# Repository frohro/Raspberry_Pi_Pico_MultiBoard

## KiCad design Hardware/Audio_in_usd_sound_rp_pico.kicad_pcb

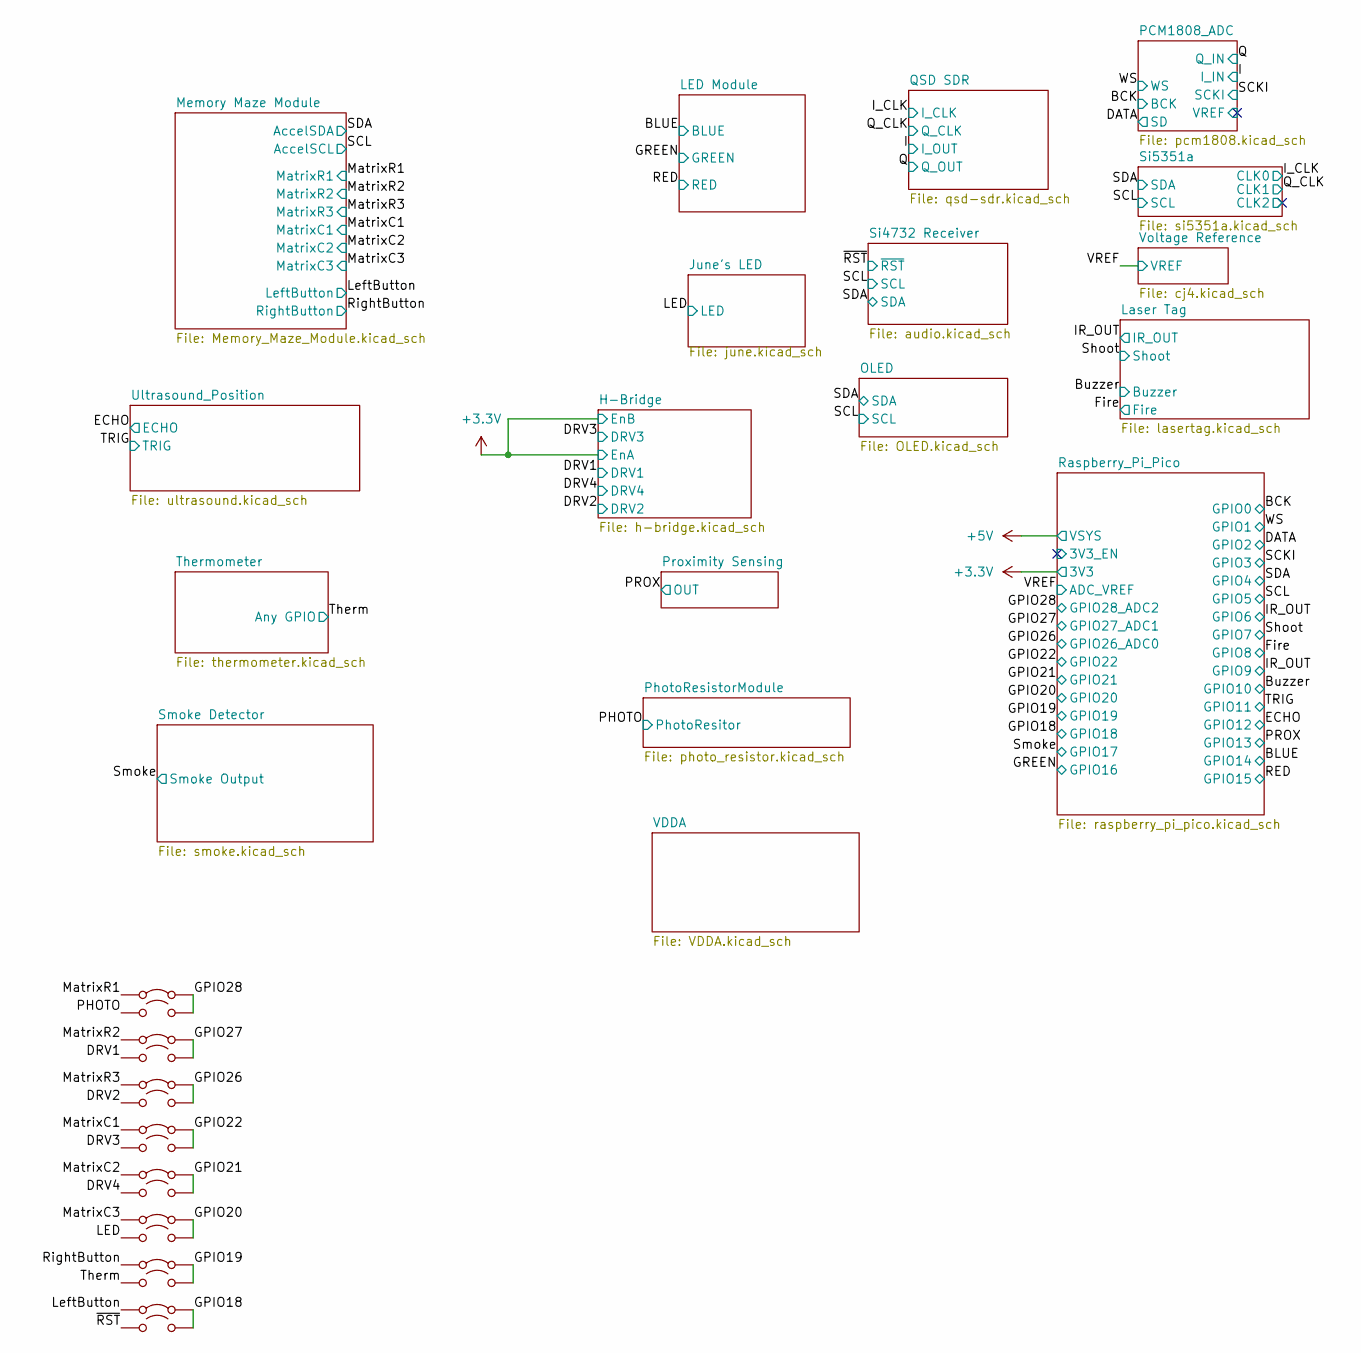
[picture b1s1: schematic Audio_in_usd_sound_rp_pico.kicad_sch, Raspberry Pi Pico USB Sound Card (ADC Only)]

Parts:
JP1, JP3, JP5, JP7, JP9, JP11, JP13, JP15: Jumper_2_Bridged; SolderJumper-2_P1.3mm_Bridged2Bar_RoundedPad1.0x1.5mm
JP2, JP4, JP6, JP8, JP10, JP12, JP14, JP16: Jumper_2_Open; SolderJumper-2_P1.3mm_Open_RoundedPad1.0x1.5mm

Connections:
/DRV1: JP4.1 (A); also elsewhere on the board
/DRV2: JP6.1 (A); also elsewhere on the board
/DRV3: JP8.1 (A); also elsewhere on the board
/DRV4: JP10.1 (A); also elsewhere on the board
/GPIO18: JP15.2 (B), JP16.2 (B); also elsewhere on the board
/GPIO19: JP13.2 (B), JP14.2 (B); also elsewhere on the board
/GPIO20: JP11.2 (B), JP12.2 (B); also elsewhere on the board
/GPIO21: JP9.2 (B), JP10.2 (B); also elsewhere on the board
/GPIO22: JP7.2 (B), JP8.2 (B); also elsewhere on the board
/GPIO26: JP5.2 (B), JP6.2 (B); also elsewhere on the board
/GPIO27: JP3.2 (B), JP4.2 (B); also elsewhere on the board
/GPIO28: JP1.2 (B), JP2.2 (B); also elsewhere on the board
/LED: JP12.1 (A); also elsewhere on the board
/LeftButton: JP15.1 (A); also elsewhere on the board
/MatrixC1: JP7.1 (A); also elsewhere on the board
/MatrixC2: JP9.1 (A); also elsewhere on the board
/MatrixC3: JP11.1 (A); also elsewhere on the board
/MatrixR1: JP1.1 (A); also elsewhere on the board
/MatrixR2: JP3.1 (A); also elsewhere on the board
/MatrixR3: JP5.1 (A); also elsewhere on the board
/PHOTO: JP2.1 (A); also elsewhere on the board
/RightButton: JP13.1 (A); also elsewhere on the board
/Therm: JP14.1 (A); also elsewhere on the board
/~RST: JP16.1 (A); also elsewhere on the board

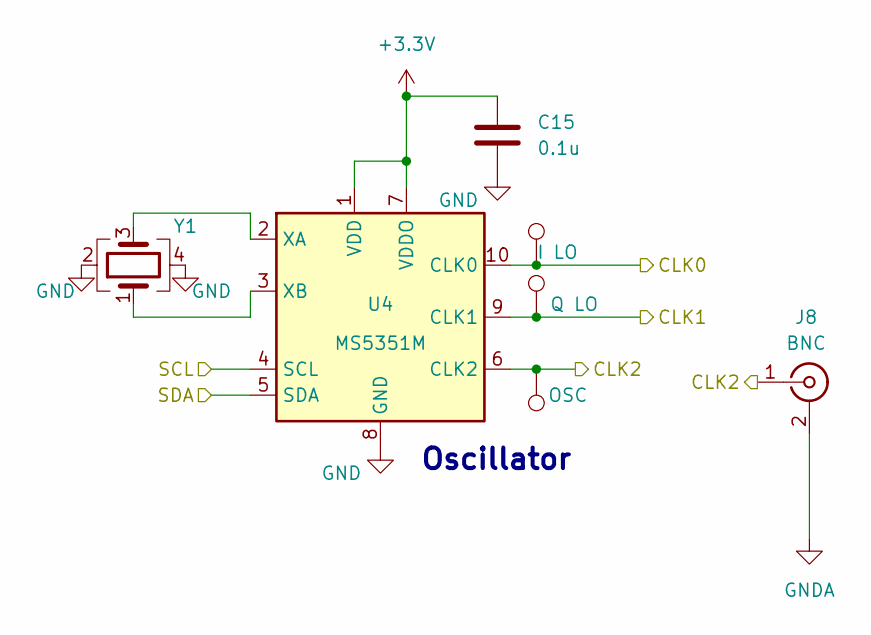
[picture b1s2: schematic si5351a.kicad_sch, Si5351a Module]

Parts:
C15: 0.1u; C_0805_2012Metric; LCSC C49678
J8: BNC; BNC_TEConnectivity_1478204_Vertical
TP3: I LO; TestPoint_THTPad_D1.0mm_Drill0.5mm
TP4: Q LO; TestPoint_THTPad_D1.0mm_Drill0.5mm
TP5: OSC; TestPoint_THTPad_D1.0mm_Drill0.5mm
U4: MS5351M; MSOP-10_3x3mm_P0.5mm; LCSC C1509083
Y1: X322525MSB4SI; Crystal_SMD_3225-4Pin_3.2x2.5mm; LCSC C9006

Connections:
+3.3V: C15.2, U4.1 (VDD), U4.7 (VDDO); also elsewhere on the board
/I_CLK: TP3.1, U4.10 (CLK0); also elsewhere on the board
/Q_CLK: TP4.1, U4.9 (CLK1); also elsewhere on the board
/SCL: U4.4 (SCL); also elsewhere on the board
/SDA: U4.5 (SDA); also elsewhere on the board
/Si5351a/CLK2: J8.1 (In), TP5.1, U4.6 (CLK2)
GND: C15.1, J8.2 (Ext), U4.8 (GND), Y1.2, Y1.4; also elsewhere on the board
unnamed: U4.2 (XA), Y1.3
unnamed: U4.3 (XB), Y1.1

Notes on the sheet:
Oscillator

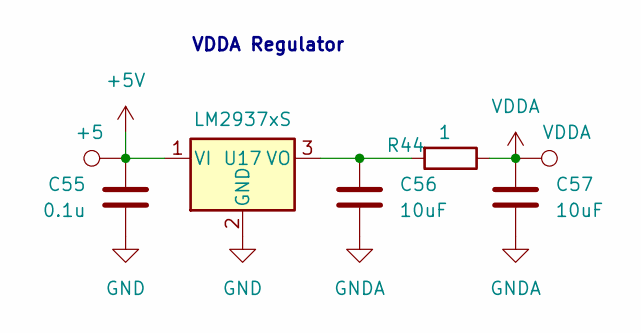
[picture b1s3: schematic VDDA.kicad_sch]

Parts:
C55: 0.1u; C_0805_2012Metric; LCSC C49678
C56, C57: 10uF; C_0805_2012Metric; LCSC C15850
R44: 1; R_0805_2012Metric; LCSC C25271
TP25: +5; TestPoint_THTPad_D1.0mm_Drill0.5mm
TP26: VDDA; TestPoint_THTPad_D1.0mm_Drill0.5mm
U17: LM2937xS; TO-263-3_TabPin2; LCSC C2902486

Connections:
+5V: C55.1, TP25.1, U17.1 (VI); also elsewhere on the board
GND: C55.2, C56.2, C57.2, U17.2 (GND); also elsewhere on the board
unnamed: C56.1, R44.2, U17.3 (VO)
VDDA: C57.1, R44.1, TP26.1; also elsewhere on the board

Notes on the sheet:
VDDA Regulator

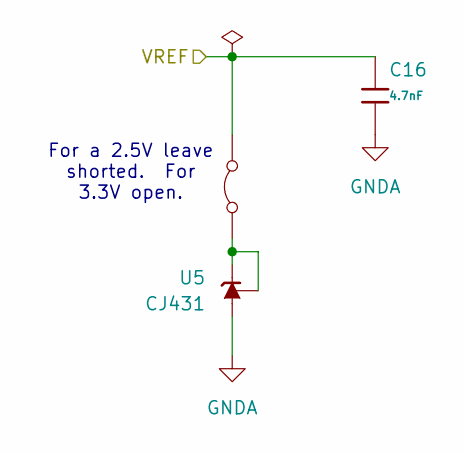
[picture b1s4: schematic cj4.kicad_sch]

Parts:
C16: 4.7nF; C_0805; Voltage Rated 50V; Tolerance ±10%; Part 0805B472K500NT; LCSC C1744
JP84: Jumper_2_Bridged; SolderJumper-2_P1.3mm_Bridged2Bar_RoundedPad1.0x1.5mm
U5: CJ431; SOT-23; JLCPCB Rotation Offset 180

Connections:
/VREF: C16.1, JP84.2 (B); also elsewhere on the board
GND: C16.2, U5.3 (A); also elsewhere on the board
unnamed: JP84.1 (A), U5.1 (REF), U5.2 (K)

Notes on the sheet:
For a 2.5V leave shorted. For 3.3V open.

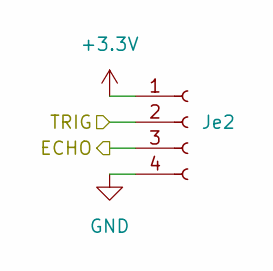
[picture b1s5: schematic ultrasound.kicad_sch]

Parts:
Je2: Conn_01x04_Socket; PinHeader_1x04_P2.54mm_Vertical_Female; LCSC C2718488

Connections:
+3.3V: Je2.1; also elsewhere on the board
/ECHO: Je2.3; also elsewhere on the board
/TRIG: Je2.2; also elsewhere on the board
GND: Je2.4; also elsewhere on the board

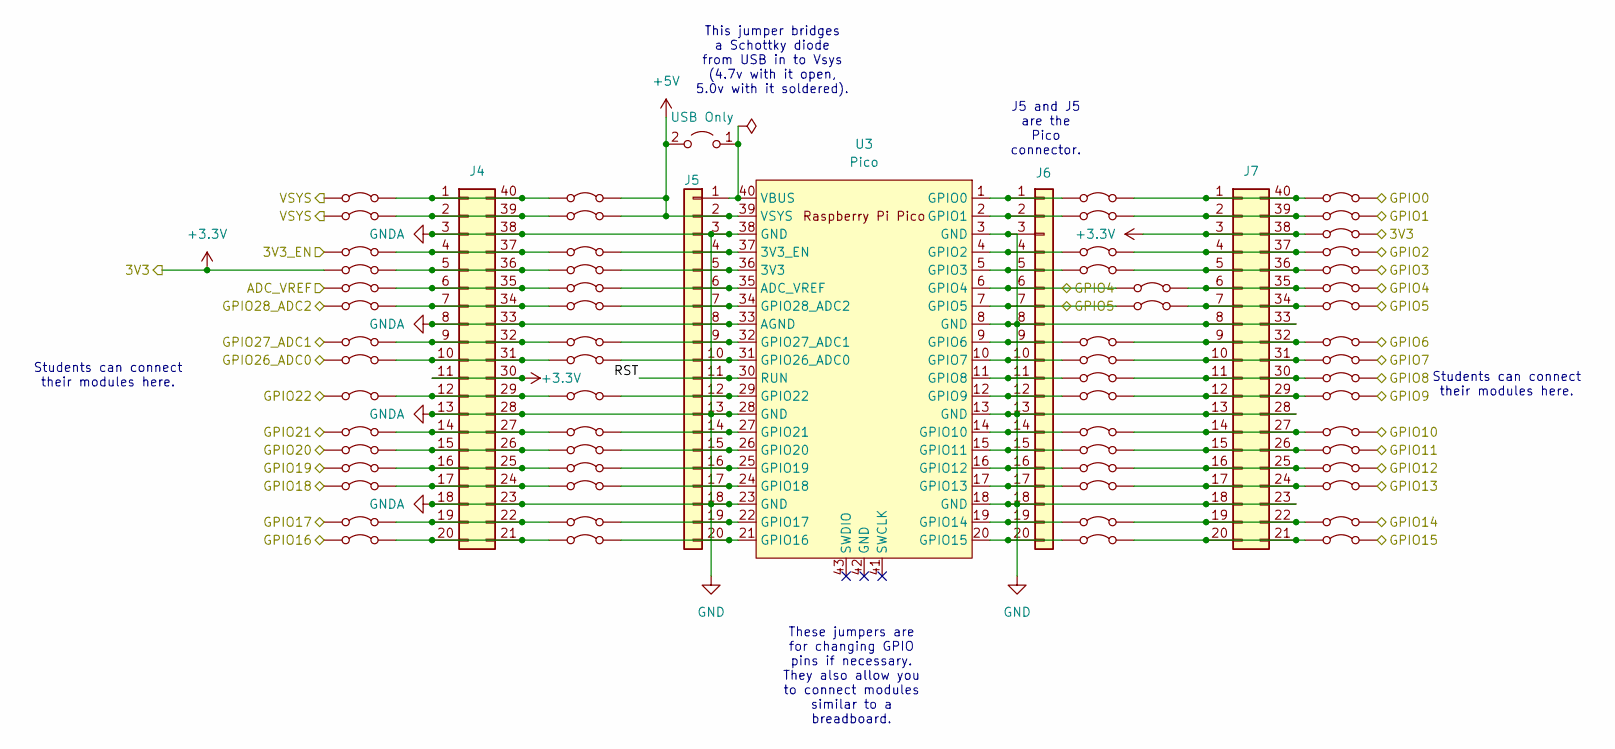
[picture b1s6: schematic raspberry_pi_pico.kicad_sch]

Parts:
J4: Conn_02x20_Counter_Clockwise; PinSocket_2x20_P2.54mm_Vertical_Counterclockwise; LCSC C2977589
J5, J6: Conn_01x20; PinHeader_1x20_P2.54mm_Vertical; LCSC C2905423
J7: Conn_02x20_Counter_Clockwise; PinSocket_2x20_P2.54mm_Vertical; LCSC C2977589
JP20, JP21, JP22, JP23, JP24, JP25, JP26, JP27, JP28, JP29, JP30, JP31, JP32, JP33, JP34, JP35, JP36, JP37, JP38, JP39, JP40, JP41, JP42, JP43, JP44, JP45, JP46, JP47, JP48, JP49, JP51, JP52, JP53, JP54, JP55, JP56, JP57, JP58, JP59, JP60, JP61, JP62, JP63, JP64, JP65, JP66, JP67, JP68, JP69, JP70, JP71, JP72, JP73, JP74, JP75, JP76, JP77, JP78, JP79, JP80, JP81, JP82, JP83: Jumper_2_Bridged; SolderJumper-2_P1.3mm_Bridged2Bar_RoundedPad1.0x1.5mm
JP50: USB Only; SolderJumper-2_P1.3mm_Open_RoundedPad1.0x1.5mm
U3: Pico; RPi_Pico_SMD_TH

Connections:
+3.3V: J4.11, J4.30, J7.3, J7.38, JP23.1 (A), JP69.1 (A), JP69.2 (B); also elsewhere on the board
+5V: J5.2, JP20.1 (A), JP21.1 (A), JP35.2 (B), JP36.2 (B), JP50.2 (B), U3.39 (VSYS); also elsewhere on the board
/BCK: JP67.2 (B); also elsewhere on the board
/BLUE: JP82.2 (B); also elsewhere on the board
/Buzzer: JP78.2 (B); also elsewhere on the board
/DATA: JP70.2 (B); also elsewhere on the board
/ECHO: JP80.2 (B); also elsewhere on the board
/Fire: JP76.2 (B); also elsewhere on the board
/GPIO18: JP32.1 (A); also elsewhere on the board
/GPIO19: JP31.1 (A); also elsewhere on the board
/GPIO20: JP30.1 (A); also elsewhere on the board
/GPIO21: JP29.1 (A); also elsewhere on the board
/GPIO22: JP28.1 (A); also elsewhere on the board
/GPIO26: JP27.1 (A); also elsewhere on the board
/GPIO27: JP26.1 (A); also elsewhere on the board
/GPIO28: JP25.1 (A); also elsewhere on the board
/GREEN: JP34.1 (A); also elsewhere on the board
/IR_OUT: JP74.2 (B), JP77.2 (B); also elsewhere on the board
/PROX: JP81.2 (B); also elsewhere on the board
/RED: JP83.2 (B); also elsewhere on the board
/Raspberry_Pi_Pico/3V3_EN: JP22.1 (A)
/Raspberry_Pi_Pico/RST: J5.11, U3.30 (RUN)
/SCKI: JP71.2 (B); also elsewhere on the board
/SCL: J6.7, JP56.1 (A), JP73.2 (B), U3.7 (GPIO5); also elsewhere on the board
/SDA: J6.6, JP55.1 (A), JP72.2 (B), U3.6 (GPIO4); also elsewhere on the board
/Shoot: JP75.2 (B); also elsewhere on the board
/Smoke: JP33.1 (A); also elsewhere on the board
/TRIG: JP79.2 (B); also elsewhere on the board
/VREF: JP24.1 (A); also elsewhere on the board
/WS: JP68.2 (B); also elsewhere on the board
GND: J4.3, J4.8, J4.13, J4.18, J4.23, J4.28, J4.33, J4.38, J5.3, J5.8, J5.13, J5.18, J6.3, J6.8, J6.13, J6.18, J7.8, J7.13, J7.18, J7.23, J7.28, J7.33, U3.3 (GND), U3.8 (GND), U3.13 (GND), U3.18 (GND), U3.23 (GND), U3.28 (GND), U3.33 (AGND), U3.38 (GND); also elsewhere on the board
unnamed: J4.1, J4.40, JP20.2 (B), JP35.1 (A)
unnamed: J4.2, J4.39, JP21.2 (B), JP36.1 (A)
unnamed: J4.10, J4.31, JP27.2 (B), JP42.1 (A)
unnamed: J4.12, J4.29, JP28.2 (B), JP43.1 (A)
unnamed: J4.14, J4.27, JP29.2 (B), JP44.1 (A)
unnamed: J4.15, J4.26, JP30.2 (B), JP45.1 (A)
unnamed: J4.16, J4.25, JP31.2 (B), JP46.1 (A)
unnamed: J4.17, J4.24, JP32.2 (B), JP47.1 (A)
unnamed: J4.19, J4.22, JP33.2 (B), JP48.1 (A)
unnamed: J4.20, J4.21, JP34.2 (B), JP49.1 (A)
unnamed: J4.9, J4.32, JP26.2 (B), JP41.1 (A)
unnamed: J4.7, J4.34, JP25.2 (B), JP40.1 (A)
unnamed: J4.6, J4.35, JP24.2 (B), JP39.1 (A)
unnamed: J4.5, J4.36, JP23.2 (B), JP38.1 (A)
unnamed: J4.4, J4.37, JP22.2 (B), JP37.1 (A)
unnamed: J5.1, JP50.1 (A), U3.40 (VBUS)
unnamed: J5.4, JP37.2 (B), U3.37 (3V3_EN)
unnamed: J5.5, JP38.2 (B), U3.36 (3V3)
unnamed: J5.6, JP39.2 (B), U3.35 (ADC_VREF)
unnamed: J5.7, JP40.2 (B), U3.34 (GPIO28_ADC2)
unnamed: J5.9, JP41.2 (B), U3.32 (GPIO27_ADC1)
unnamed: J5.10, JP42.2 (B), U3.31 (GPIO26_ADC0)
unnamed: J5.12, JP43.2 (B), U3.29 (GPIO22)
unnamed: J5.14, JP44.2 (B), U3.27 (GPIO21)
unnamed: J5.15, JP45.2 (B), U3.26 (GPIO20)
unnamed: J5.16, JP46.2 (B), U3.25 (GPIO19)
unnamed: J5.17, JP47.2 (B), U3.24 (GPIO18)
unnamed: J5.19, JP48.2 (B), U3.22 (GPIO17)
unnamed: J5.20, JP49.2 (B), U3.21 (GPIO16)
unnamed: J6.1, JP51.1 (A), U3.1 (GPIO0)
unnamed: J6.2, JP52.1 (A), U3.2 (GPIO1)
unnamed: J6.4, JP53.1 (A), U3.4 (GPIO2)
unnamed: J6.5, JP54.1 (A), U3.5 (GPIO3)
unnamed: J6.9, JP57.1 (A), U3.9 (GPIO6)
unnamed: J6.10, JP58.1 (A), U3.10 (GPIO7)
unnamed: J6.11, JP59.1 (A), U3.11 (GPIO8)
unnamed: J6.12, JP60.1 (A), U3.12 (GPIO9)
unnamed: J6.14, JP61.1 (A), U3.14 (GPIO10)
unnamed: J6.15, JP62.1 (A), U3.15 (GPIO11)
unnamed: J6.16, JP63.1 (A), U3.16 (GPIO12)
unnamed: J6.17, JP64.1 (A), U3.17 (GPIO13)
unnamed: J6.19, JP65.1 (A), U3.19 (GPIO14)
unnamed: J6.20, JP66.1 (A), U3.20 (GPIO15)
unnamed: J7.1, J7.40, JP51.2 (B), JP67.1 (A)
unnamed: J7.2, J7.39, JP52.2 (B), JP68.1 (A)
unnamed: J7.10, J7.31, JP58.2 (B), JP75.1 (A)
unnamed: J7.11, J7.30, JP59.2 (B), JP76.1 (A)
unnamed: J7.12, J7.29, JP60.2 (B), JP77.1 (A)
unnamed: J7.14, J7.27, JP61.2 (B), JP78.1 (A)
unnamed: J7.15, J7.26, JP62.2 (B), JP79.1 (A)
unnamed: J7.16, J7.25, JP63.2 (B), JP80.1 (A)
unnamed: J7.17, J7.24, JP64.2 (B), JP81.1 (A)
unnamed: J7.19, J7.22, JP65.2 (B), JP82.1 (A)
unnamed: J7.20, J7.21, JP66.2 (B), JP83.1 (A)
unnamed: J7.9, J7.32, JP57.2 (B), JP74.1 (A)
unnamed: J7.7, J7.34, JP56.2 (B), JP73.1 (A)
unnamed: J7.6, J7.35, JP55.2 (B), JP72.1 (A)
unnamed: J7.5, J7.36, JP54.2 (B), JP71.1 (A)
unnamed: J7.4, J7.37, JP53.2 (B), JP70.1 (A)

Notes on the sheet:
These jumpers are for changing GPIO pins if necessary. They also allow you to connect modules similar to a breadboard.
Students can connect their modules here.
J5 and J5 are the Pico connector.
This jumper bridges a Schottky diode from USB in to Vsys (4.7v with it open, 5.0v with it soldered).

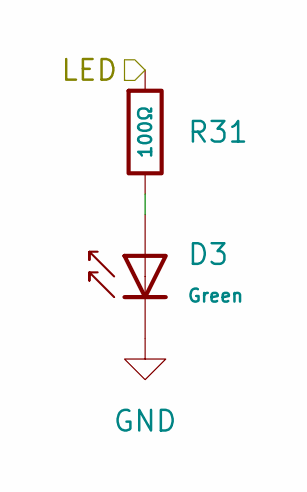
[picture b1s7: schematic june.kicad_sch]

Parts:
D3: Green; D_0805; Part KT-0805G; LCSC C2297
R31: 100Ω; R_0805; Overload Voltage (Max) 150V; Tolerance ±1%; Part 0805W8F1000T5E; LCSC C17408

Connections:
/LED: R31.1; also elsewhere on the board
GND: D3.1; also elsewhere on the board
unnamed: D3.2, R31.2

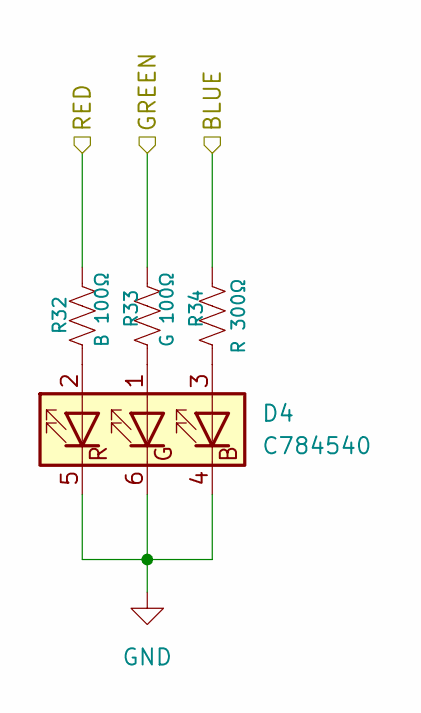
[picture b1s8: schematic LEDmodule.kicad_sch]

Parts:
D4: C784540; LED footprint; LCSC C784540
R32: B 100Ω; L_0805_2012Metric; JLCPCB# C25277
R33: G 100Ω; L_0805_2012Metric; JLCPCB# C25277
R34: R 300Ω; R_0805_2012Metric; JLCPCB# C168494

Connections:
/BLUE: R34.1; also elsewhere on the board
/GREEN: R33.1; also elsewhere on the board
/RED: R32.1; also elsewhere on the board
GND: D4.4 (BK), D4.5 (RK), D4.6 (GK); also elsewhere on the board
unnamed: D4.3 (BA), R34.2
unnamed: D4.1 (GA), R33.2
unnamed: D4.2 (RA), R32.2

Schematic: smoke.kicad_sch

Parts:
R43: 100Ω; R_0805; Overload Voltage (Max) 150V; Tolerance ±1%; Part 0805W8F1000T5E; LCSC C17408
U16: TO-33-4_Window-Taylan; LCSC C5380082

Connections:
+3.3V: U16.3 (VC); also elsewhere on the board
+5V: U16.1 (V0_1); also elsewhere on the board
/Smoke: R43.1, U16.4 (V(RL)); also elsewhere on the board
<NO NET>: R43.2, U16.2 (V0_2)

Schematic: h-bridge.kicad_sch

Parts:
C49, C50: 100nF; C_0805; Voltage Rated 50V; Tolerance ±10%; Part CC0805KRX7R9BB104; LCSC C49678
D5, D6, D7, D8, D9, D10, D11, D12: 1N4004W; D_SOD-123FL; Forward Voltage (Vf@If) 1V@1.0A; Reverse Voltage (Vr) 400V; Part 1N4004W; LCSC C18199087
J16: Audio IN; Jack_3.5mm_CUI_SJ-3523-SMT_Horizontal; LCSC C18594
JP89: Jumper_2_Bridged; SolderJumper-2_P1.3mm_Bridged2Bar_RoundedPad1.0x1.5mm
T1, T2: Screw Terminal, 4Px5.08mm, 20A; CONN-TH_4P-P5.08_DB129VG-5.08-4P-GN-S; Current Rating (Max) 20A; Voltage Rating (Max) 300V; Part DB129VG-5.08-4P-GN-S; LCSC C2981774
U12: L298N; TO-220-15_P2.54x2.54mm_StaggerOdd_Lead4.58mm_Vertical; JLCPCB part # C19922

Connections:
+3.3V: U12.6 (EnA), U12.11 (EnB); also elsewhere on the board
+5V: JP89.1 (A), U12.9 (Vss); also elsewhere on the board
/DRV1: U12.5 (IN1); also elsewhere on the board
/DRV2: U12.7 (IN2); also elsewhere on the board
/DRV3: U12.10 (IN3); also elsewhere on the board
/DRV4: U12.12 (IN4); also elsewhere on the board
GND: C49.2, C50.2, D6.2, D8.2, D10.2, D12.2, J16.S, T1.4, U12.8 (GND); also elsewhere on the board
unnamed: D7.2, D8.1, J16.R, T2.1, U12.2 (OUT1)
unnamed: D11.2, D12.1, J16.T, T2.2, U12.3 (OUT2)
unnamed: D5.2, D6.1, T2.3, U12.13 (OUT3)
unnamed: D9.2, D10.1, T2.4, U12.14 (OUT4)
unnamed: T1.2, U12.1 (SENSE_A)
unnamed: T1.1, U12.15 (SENSE_B)
VS: C49.1, C50.1, D5.1, D7.1, D9.1, D11.1, JP89.2 (B), T1.3, U12.4 (Vs)

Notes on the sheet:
Resistors

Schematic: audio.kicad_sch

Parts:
C33, C42: 220pF; C_0805; Voltage Rated 50V; Tolerance ±10%; Part CC0805KRX7R9BB221; LCSC C107145
C34, C43: 10nF; C_0603; Voltage Rated 50V; Tolerance ±10%; Part 0603B103K500NT; LCSC C57112
C35, C54: 2.2nF; C_0603; Voltage Rated 50V; Tolerance ±10%; Part 0603B222K500NT; LCSC C1604
C36, C37: 22pF; C_0603; Voltage Rated 50V; Tolerance ±5%; Part CL10C220JB8NNNC; LCSC C1653
C38, C41, C52: 100nF; C_0603; Voltage Rated 50V; Tolerance ±10%; Part CC0603KRX7R9BB104; LCSC C14663
C39, C40, C44, C45: 10uF; C_0805; Voltage Rated 25V; Tolerance ±10%; Part CL21A106KAYNNNE; LCSC C15850
C46: 1uF; C_0805; Voltage Rated 50V; Tolerance ±10%; Part CL21B105KBFNNNE; LCSC C28323
J13, J14: ANT_BNC; BNC_TEConnectivity_1478204_Vertical
J15: Audio IN; Jack_3.5mm_CUI_SJ-3523-SMT_Horizontal; LCSC C18594
Q3: MMBT2222A; Q_SOT-23; Part MMBT2222A; LCSC C7420351
R10, R20: 39kΩ; R_0603; Overload Voltage (Max) 75V; Tolerance ±1%; Part 0603WAF3902T5E; LCSC C23153
R19, R25: 15k; R_0805_2012Metric; LCSC C17475
R21, R27: 8.2k; R_0805_2012Metric; LCSC C17828
R22: 100kΩ; R_0603; Overload Voltage (Max) 75V; Tolerance ±1%; Part 0603WAF1003T5E; LCSC C25803
R23, R28: 3.9k; R_0805_2012Metric; LCSC C17614
R24: 1k; R_1206_3216Metric; LCSC C4410
R29, R30: 2kΩ; R_0805; Overload Voltage (Max) 150V; Tolerance ±1%; Part 0805W8F2001T5E; LCSC C17604
U9: LM358; SOP-8_3.9x4.9mm_P1.27mm
U10: Si4732; SOIC-16_3.9x9.9mm_P1.27mm; LCSC C2155558
X1: Q13FC1350000400; FC-135R_L3.2-W1.5; Frequency Tolerance ±20ppm; Part Q13FC13500004; LCSC C32346

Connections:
+3.3V: C52.2, U10.11 (VDD); also elsewhere on the board
+5V: C38.1, R22.2, R24.1, R29.1, U9.8 (V+); also elsewhere on the board
/SCL: U10.14 (SCLK); also elsewhere on the board
/SDA: U10.13 (SDIO); also elsewhere on the board
/~RST: U10.16 (~RST); also elsewhere on the board
GND: C36.1, C37.2, C38.2, C46.2, C52.1, J13.2 (Ext), J14.2 (Ext), J15.S, Q3.2 (E), R30.2, U9.4 (V-), U10.7 (RFGND), U10.10 (GND), U10.15 (~SEN); also elsewhere on the board
GND1: C35.2, C46.1, C54.2, R19.2, R21.2, R25.2, R27.2, R29.2, R30.1
unnamed: C33.1, C39.2, R10.1, U9.1
unnamed: C39.1, J15.R
unnamed: C40.1, R23.2
unnamed: C42.1, C44.2, R20.1, U9.7
unnamed: C44.1, J15.T
unnamed: C45.1, R28.1
unnamed: C43.1, J13.1 (In)
unnamed: C34.1, J14.1 (In)
unnamed: C43.2, Q3.1 (B), R22.1
unnamed: C41.2, Q3.3 (C), R24.2
unnamed: C35.1, R21.1, R23.1, U9.3 (+)
unnamed: C33.2, R10.2, R19.1, U9.2 (-)
unnamed: C54.1, R27.1, R28.2, U9.5 (+)
unnamed: C42.2, R20.2, R25.1, U9.6 (-)
unnamed: C41.1, U10.8 (AMI)
unnamed: C37.1, U10.2 (DCLK), X1.1
unnamed: C34.2, U10.6 (FMI)
unnamed: C40.2, U10.1 (LOUT)
unnamed: C36.2, U10.12 (RCLK), X1.2
unnamed: C45.2, U10.9 (ROUT)

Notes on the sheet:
The pin numbers are wrong for the Si4732. The right side is reversed.

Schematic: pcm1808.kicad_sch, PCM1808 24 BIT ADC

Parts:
C3, C4: 1uF; C_0805_2012Metric; LCSC C28323
C6, C7: 4.7nF; C_0805; Voltage Rated 50V; Tolerance ±10%; Part 0805B472K500NT; LCSC C1744
C8, C9, C12: 10uF; C_0805_2012Metric; LCSC C15850
C10, C13: 0.1uF; C_0805_2012Metric; LCSC C49678
C11: 0.1u; C_0805_2012Metric; LCSC C49678
C14: 220pF; C_0805; Voltage Rated 50V; Tolerance ±10%; Part CC0805KRX7R9BB221; LCSC C107145
J1: ADC IN; Jack_3.5mm_CUI_SJ-3523-SMT_Horizontal; LCSC C18594
JP17: Jumper_2_Bridged; SolderJumper-2_P1.3mm_Bridged2Bar_RoundedPad1.0x1.5mm
JP18, JP19: GND_LP_SND; SolderJumper-2_P1.3mm_Open_RoundedPad1.0x1.5mm
R2, R3: 200; R_0805_2012Metric; LCSC C17544
TP1: L; TestPoint_THTPad_D1.0mm_Drill0.5mm
TP2: R; TestPoint_THTPad_D1.0mm_Drill0.5mm
U2: PCM1808PWR; TSSOP-14_4.4x5mm_P0.65mm; PARTREV B; LCSC C55513

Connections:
+3.3V: C8.1, C10.2, U2.4 (VDD); also elsewhere on the board
/BCK: U2.8 (BCK); also elsewhere on the board
/DATA: U2.9 (DOUT); also elsewhere on the board
/I: JP18.2 (B); also elsewhere on the board
/PCM1808_ADC/VREF: C9.1, C11.2, U2.1 (VREF)
/Q: JP19.1 (A); also elsewhere on the board
/SCKI: U2.6 (SCKI); also elsewhere on the board
/WS: C14.1, U2.7 (LRCK); also elsewhere on the board
GND: C6.2, C7.2, C8.2, C9.2, C10.1, C11.1, C12.2, C13.1, C14.2, JP17.1 (A), U2.2 (AGND), U2.5 (DGND), U2.10 (MD0), U2.11 (MD1), U2.12 (FMT); also elsewhere on the board
unnamed: C3.2, R2.1
unnamed: C4.2, R3.1
unnamed: J1.S, JP17.2 (B)
unnamed: C3.1, J1.R, JP18.1 (A), TP1.1
unnamed: C4.1, J1.T, JP19.2 (B), TP2.1
unnamed: C6.1, R2.2, U2.13 (VINL)
unnamed: C7.1, R3.2, U2.14 (VINR)
VDDA: C12.1, C13.2, U2.3 (VCC); also elsewhere on the board

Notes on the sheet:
Jumper for ground loop mediation
GND and GNDA all the same second layer from the top.
24 Bit ADC
BCK
Data (SD)
Capacitor found necessary in first prototype.
LRCK (WS)

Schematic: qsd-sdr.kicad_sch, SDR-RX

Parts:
C18, C19, C25, C26: 1uF; C_0805; Voltage Rated 50V; Tolerance ±10%; Part CL21B105KBFNNNE; LCSC C28323
C20, C23, C30: 0.1u; C_0805_2012Metric; LCSC C49678
C21, C22, C24, C27: 4.7nF; C_0805; Voltage Rated 50V; Tolerance ±10%; Part 0805B472K500NT; LCSC C1744
C28, C29: 100pF; C_0805; Voltage Rated 50V; Tolerance ±5%; Part CL21C101JBANNNC; LCSC C1790
C31, C32: 10uF; C_0805; Voltage Rated 25V; Tolerance ±10%; Part CL21A106KAYNNNE; LCSC C15850
J11: SDR ANT; BNC_TEConnectivity_1478204_Vertical
J12: SDR Out; Jack_3.5mm_CUI_SJ-3523-SMT_Horizontal; LCSC C18594
JP85: Groundloop RX_NS; SolderJumper-2_P1.3mm_Open_RoundedPad1.0x1.5mm
JP86, JP87: Jumper_2_Bridged; SolderJumper-2_P1.3mm_Bridged2Bar_RoundedPad1.0x1.5mm
JP88: GND_LP_SND; SolderJumper-2_P1.3mm_Open_RoundedPad1.0x1.5mm
Je3: Filter; PinHeader_1x04_P2.54mm_Vertical_Female; LCSC C2718488
R1: 10kΩ; R_0603; Overload Voltage (Max) 75V; Tolerance ±1%; Part 0603WAF1002T5E; LCSC C25804
R11: 1kΩ; R_0603; Overload Voltage (Max) 75V; Tolerance ±1%; Part 0603WAF1001T5E; LCSC C21190
R12: 10k; R_0805_2012Metric; LCSC C17414
R13, R14, R15, R16: 10Ω; R_0805; Overload Voltage (Max) 150V; Tolerance ±1%; Part 0805W8F100JT5E; LCSC C17415
R17, R18: 2kΩ; R_0805; Overload Voltage (Max) 150V; Tolerance ±1%; Part 0805W8F2001T5E; LCSC C17604
TP10, TP12: GND; TestPoint_THTPad_D2.0mm_Drill1.0mm
TP11: VA/2; TestPoint_THTPad_D1.0mm_Drill0.5mm
TP13: 180; TestPoint_THTPad_D1.0mm_Drill0.5mm
TP14: 0; TestPoint_THTPad_D1.0mm_Drill0.5mm
TP15: 270; TestPoint_THTPad_D1.0mm_Drill0.5mm
TP16: 90; TestPoint_THTPad_D1.0mm_Drill0.5mm
TP17: I; TestPoint_THTPad_D1.0mm_Drill0.5mm
TP18: Q; TestPoint_THTPad_D1.0mm_Drill0.5mm
U7: PI5C3253CQEX; SSOP-16_3.9x4.9mm_P0.635mm; LCSC C3001703
U8: OPA1612AxD; SOIC-8_3.9x4.9mm_P1.27mm; LCSC C94590

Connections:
/I: C28.2, C31.1, R17.2, TP17.1, U8.7; also elsewhere on the board
/I_CLK: U7.14 (S0); also elsewhere on the board
/Q: C29.2, C32.1, R18.2, TP18.1, U8.1; also elsewhere on the board
/Q_CLK: U7.2 (S1); also elsewhere on the board
GND: C20.1, C21.2, C22.2, C23.1, C24.2, C27.2, C30.1, JP85.1 (A), JP88.1 (A), Je3.2, Je3.3, R1.1, TP10.1, TP12.1, U7.1 (1~OE), U7.8 (GND), U7.15 (2~OE), U8.4 (V-); also elsewhere on the board
unnamed: C20.2, R1.2, R11.1, R12.2, TP11.1
unnamed: C25.2, R13.1, TP13.1
unnamed: C26.2, R16.1, TP15.1
unnamed: C31.2, J12.R
unnamed: C32.2, J12.T
unnamed: J11.2 (Ext), JP85.2 (B)
unnamed: C18.1, J11.1 (In)
unnamed: C18.2, JP86.1 (A), Je3.1
unnamed: C19.1, JP86.2 (B), Je3.4
unnamed: JP87.1 (A), U7.7 (1A)
unnamed: C19.2, JP87.2 (B), R11.2, U7.9 (2A)
unnamed: J12.S, JP88.2 (B)
unnamed: C25.1, C27.1, U7.6 (1B1), U7.10 (2B1)
unnamed: C24.1, R15.1, TP16.1, U7.5 (1B2), U7.11 (2B2)
unnamed: C22.1, C26.1, U7.4 (1B3), U7.12 (2B3)
unnamed: C21.1, R14.1, TP14.1, U7.3 (1B4), U7.13 (2B4)
unnamed: R15.2, U8.3 (+)
unnamed: C29.1, R16.2, R18.1, U8.2 (-)
unnamed: R14.2, U8.5 (+)
unnamed: C28.1, R13.2, R17.1, U8.6 (-)
VDDA: C23.2, C30.2, R12.1, U7.16 (VCC), U8.8 (V+); also elsewhere on the board

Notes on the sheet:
Why are these 10k different?
Sequence of clocks: Q_CLK, I_CLK 0 degrees: 1,1 90 degrees: 1,0 180 degrees: 0,0 270 degrees: 0,1
Amplifier/Filter
Ground Loop Remediation
Mixer
Mixer 1 or 2
Scope GND connections
External Filter Option

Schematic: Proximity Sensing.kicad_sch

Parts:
C51: 100nF; C_0805; Voltage Rated 50V; Tolerance ±10%; Part CC0805KRX7R9BB104; LCSC C49678
IR-LED1: IR26-21C_L110_TR8; LED_1206_3216Metric; LCSC C965892
IR-PD1: D_Photo; LED_D5.0mm; LCSC C965891
R35: 10K; R_0805_2012Metric; Part # C17414
R36: 270R; R_0805_2012Metric; Part # 0805W8F1002T5E
RV2: R_Potentiometer_US; Potentiometer_Piher_PT-6-V_Vertical_Hole
U13: LM393DR2G; SOIC-8_L5.0-W4.0-P1.27-LS6.0-BL; Supply Voltage 2V~36V;1V~18V; Part LM393DR2G; LCSC C7955

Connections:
+3.3V: C51.1, IR-LED1.2 (A), IR-PD1.2 (A), RV2.1, U13.8 (VCC); also elsewhere on the board
/PROX: U13.7 (OUT/B); also elsewhere on the board
GND: C51.2, R35.2, R36.2, RV2.3, U13.4 (GND); also elsewhere on the board
unnamed: IR-LED1.1 (K), R36.1
unnamed: IR-PD1.1 (K), R35.1, U13.5 (IN/B)
unnamed: RV2.2, U13.6 (IN/B/2)

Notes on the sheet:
POT 10K

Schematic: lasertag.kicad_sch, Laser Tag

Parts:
C17: 0.1uF; C_0805_2012Metric
D1: Green; D_0805; Part KT-0805G; LCSC C2297
D2: IR LED IR908-7C-F; LED_D1.8mm_W1.8mm_H2.4mm_Horizontal_O1.27mm_Z8.2mm; LCSC C183794
LS1: Speaker; Buzzer_12x9.5RM7.6; LCSC C409842
Q1, Q2: MMBT2222A 1P; Q_SOT-23; Part MMBT2222A 1P; LCSC C8512
R4: 100Ω; R_0805; Overload Voltage (Max) 150V; Tolerance ±1%; Part 0805W8F1000T5E; LCSC C17408
R5: 68Ω; R_0805; Overload Voltage (Max) 150V; Tolerance ±1%; Part 0805W8F680JT5E; LCSC C17802
R6: 10kΩ; R_0805; Overload Voltage (Max) 150V; Tolerance ±1%; Part 0805W8F1002T5E; LCSC C17414
R7, R8: 1kΩ; R_0805; Overload Voltage (Max) 150V; Tolerance ±1%; Part 0805W8F1001T5E; LCSC C17513
R9: 33Ω; R_0805; Overload Voltage (Max) 150V; Tolerance ±1%; Part 0805W8F330JT5E; LCSC C17634
S2: Tactile Button, 160gf; SW-SMD_4P-L5.1-W5.1-P3.70-LS6.5-TL-2; Voltage Rating (Dc) 12V; Part TS-1187A-B-A-B; LCSC C318884
U6: TSOP4438; Vishay_MOLD-3Pin; LCSC C124647

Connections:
+3.3V: R6.1, R9.2; also elsewhere on the board
+5V: D1.2, D2.2 (A), LS1.1; also elsewhere on the board
/Buzzer: R8.2; also elsewhere on the board
/Fire: R6.2, S2.3 (C); also elsewhere on the board
/IR_OUT: U6.1 (OUT); also elsewhere on the board
/Shoot: R7.2; also elsewhere on the board
GND: C17.2, Q1.2 (E), Q2.2 (E), S2.2 (B), U6.2 (GND); also elsewhere on the board
unnamed: D1.1, R4.1
unnamed: D2.1 (K), R5.1
unnamed: Q1.1 (B), R7.1
unnamed: Q1.3 (C), R4.2, R5.2
unnamed: Q2.1 (B), R8.1
unnamed: LS1.2, Q2.3 (C)
unnamed: C17.1, R9.1, U6.3 (Vs)

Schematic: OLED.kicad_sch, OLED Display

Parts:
C48: 100nF; C_0603; Voltage Rated 50V; Tolerance ±10%; Part CC0603KRX7R9BB104; LCSC C14663
Je1: Conn_01x04_Socket; PinHeader_1x04_P2.54mm_Vertical_Female; LCSC C2718488
U11: HS96L03W2C03; OLED; LCSC C5248080

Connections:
+3.3V: C48.1, Je1.2; also elsewhere on the board
/SCL: Je1.3; also elsewhere on the board
/SDA: Je1.4; also elsewhere on the board
GND: C48.2, Je1.1; also elsewhere on the board

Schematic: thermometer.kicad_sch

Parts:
J17: Mini-jack socket; Jack_3.5mm_CUI_SJ-3523-SMT_Horizontal; LCSC C18594
J18: AudioPlug3
R42: 10kΩ; R_0805; Overload Voltage (Max) 150V; Tolerance ±1%; Part 0805W8F1002T5E; LCSC C17414
U15: DS18B20A10T6; TO-92_Inline; LCSC C22360667

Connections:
+3.3V: J17.R, R42.1; also elsewhere on the board
/Therm: J17.T, R42.2; also elsewhere on the board
GND: J17.S; also elsewhere on the board
unnamed: J18.T, U15.2 (DQ)
unnamed: J18.S, U15.1 (GND)
unnamed: J18.R, U15.3 (V_{DD})

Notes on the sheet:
Will JLCPCB solder this up for us?

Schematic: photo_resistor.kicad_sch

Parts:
R37: PhotoResistor; R_LDR_5.1x4.3mm_P3.4mm_Vertical; JLCPCB Part # C10077
R38: 1kΩ; R_1206_3216Metric; JLCPCB Part # C17902

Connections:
+3.3V: R37.2; also elsewhere on the board
/PHOTO: R37.1, R38.2; also elsewhere on the board
GND: R38.1; also elsewhere on the board

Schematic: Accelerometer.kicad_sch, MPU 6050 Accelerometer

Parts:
C2, C47: 100nF; C_0603; Voltage Rated 50V; Tolerance ±10%; Part CC0603KRX7R9BB104; LCSC C14663
U1: LSM6DSO32TR; LGA-14L_2P5X3X0P83_STM

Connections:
+3.3V: C2.2, C47.2, U1.5 (VDDIO), U1.8 (VDD), U1.12 (CS); also elsewhere on the board
/SCL: U1.13 (SCL); also elsewhere on the board
/SDA: U1.14 (SDA); also elsewhere on the board
GND: C2.1, C47.1, U1.6 (GND), U1.7 (GND); also elsewhere on the board

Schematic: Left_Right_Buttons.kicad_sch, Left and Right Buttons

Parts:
SW1: Left; SW-SMD_4P-L5.1-W5.1-P3.70-LS6.5-TL-2; LCSC C318884
SW2: Right; SW-SMD_4P-L5.1-W5.1-P3.70-LS6.5-TL-2; LCSC C318884

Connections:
/LeftButton: SW1.1; also elsewhere on the board
/RightButton: SW2.2; also elsewhere on the board
GND: SW1.2, SW2.1; also elsewhere on the board

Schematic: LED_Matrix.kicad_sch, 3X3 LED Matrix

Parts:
D13, D14, D15, D16, D17, D18, D19, D20, D21: LED; LED_0805_2012Metric; LCSC C84256
R39, R40, R41: 680; R_0805_2012Metric; LCSC C17798
TP:C1, TP:C2, TP:C3: TestPoint; TestPoint_THTPad_D1.0mm_Drill0.5mm
TP:R1, TP:R2, TP:R3: TestPoint; TestPoint_THTPad_D1.0mm_Drill0.5mm

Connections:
/MatrixC1: R39.1, TP:R1.1; also elsewhere on the board
/MatrixC2: R40.1, TP:R2.1; also elsewhere on the board
/MatrixC3: R41.1, TP:R3.1; also elsewhere on the board
/MatrixR1: D13.1 (K), D14.1 (K), D15.1 (K), TP:C1.1; also elsewhere on the board
/MatrixR2: D16.1 (K), D17.1 (K), D18.1 (K), TP:C2.1; also elsewhere on the board
/MatrixR3: D19.1 (K), D20.1 (K), D21.1 (K), TP:C3.1; also elsewhere on the board
unnamed: D13.2 (A), D16.2 (A), D19.2 (A), R39.2
unnamed: D14.2 (A), D17.2 (A), D20.2 (A), R40.2
unnamed: D15.2 (A), D18.2 (A), D21.2 (A), R41.2
